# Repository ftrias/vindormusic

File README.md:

Vindor ES Source Code
=====================

This repository holds the source code, modules and PCB layouts of the Vindor ES1/2 electronic saxophone and wind instrument (clarinet, flute, trumpet, etc.). More information is available at [Vindor Music](http://vindormusic.com)

Directories
-----------

| Directory           | Contents
| ------------------- | ------------------------
| /apps               | Mobile and web apps
| /apps/juce-gui      | Main control app for Mac/Win/iOS/Android
| /apps/splayer       | Free generic MIDI player
| /firmware           | Source for firmware and related modules
| /firmware/source    | ES1/2 main source
| /firmware/external  | Non-Vindor open source libraries used
| /pcb                | KiCad source for PCB
| /shell              | Solidworks models for the shell
| /documents          | Documentation and promotional material
| /sounds             | Sound files for use on SD cards

License
-------

Unless otherwise noted, the software is Copyright (c) 2023 by Fernando Trias and Vindor Music, Inc. The software is licensed for use under the Creative Commons license available in `LICENSE.txt` and summarized on the [CC page](https://creativecommons.org/licenses/by-nc/3.0/).

This software uses external modules that are distributed according to their own licenses, which are all open source.

To summarize:
1. You may freely use this software for non-commercial purposes.
2. You must give appropriate credit to respective authors.

History
---------
This project began in 2016 to produce an affordable electronic wind instrument. At that time, the market was dominated by Yamaha and Akai. Both produced superb instruments that were prohibitively expensive for casual musicians. In addition, there were a number of small niche manufacturers targeting advanced players. Although Akai produced a low-cost USB instrument, it was large, heavy and had limited market penetration. In addition, we wanted to create an easy-to-use low-cost alternative for beginning players that would be both stand-alone and interface easily with Garageband and similar apps popular with younger musicians.

The Vindor began with a Kickstarter campaign and started being sold commercially in 2018 both online and in stores. It was covered by numerous blogs and journals, including Fast Company and the Boston Globe. In 2019, Roland release the Aerophone Mini AE-01, which although larger and slightly more expensive than the Vindor, targeted the same entry-level market. This, combined with the COVID shutdown and subsequent rise in component costs, made producing more Vindors impractical and all existing inventory was sold out by late 2020. 

By 2023, the chip market had not recovered and it still not possible to make more Vindors (the main CPU is still unavailable). Since Vindor Music closed its doors, we have decided to open source the firmware and apps, as well as the PCB, BOM and other components.

Open Source Announcement
------------------------

Vindor Music has open sourced the ES1 electronic wind instrument software and hardware. The Vindor ES1 was a low-cost entry-level electronic wind instrument that launched in 2018 and sold until 2020, a casualty of the COVID pandemic. The release includes all the source for the firmware, Android, iOS, Mac and Windows apps, as well as the BOM, schematics and PCB layout of the circuit boards. It includes everything you need to make your own ES1 and program it to do whatever you like. We hope this will inspire hobbyists to port the ES1 to a new CPU and continue the mission of providing an affordable and functional electronic wind instrument. The source can be found at https://github.com/ftrias/vindormusic.

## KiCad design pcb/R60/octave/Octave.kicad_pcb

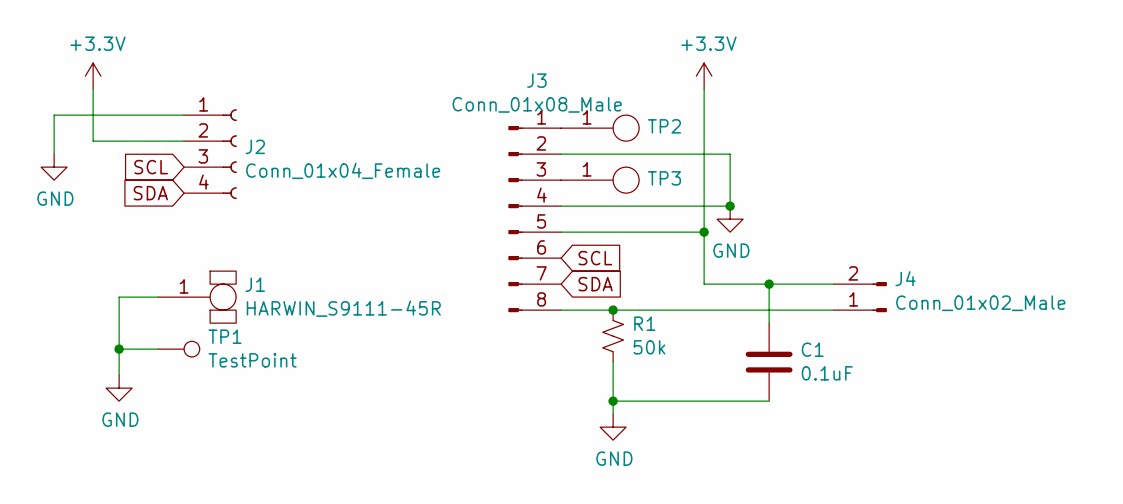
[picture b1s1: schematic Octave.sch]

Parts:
C1: 0.1uF; MF_Passives-C0603; MPN MF-CAP-0603-0.1uF
J1: HARWIN_S9111-45R; HARWIN_S9111_45R; MPN S9111-45
J2: Conn_01x04_Female; Moldex-0448120004; MPN 44812-0004
J3: Conn_01x08_Male; PinHeader_1x08_P2.54mm_Vertical; MPN MF-CON-2.54mm-01x08
J4: Conn_01x02_Male; JST_PH_S2B-PH-K_1x02_P2.00mm_Horizontal; MPN S2B-PH-K-S(LF)(SN)
R1: 50k; MF_Passives-R0603; MPN MF-RES-0603-50K
TP1: TestPoint; PinHeader_1x01_P2.54mm_Horizontal
TP2, TP3: TOUCHPAD; Vindor_Touchpad

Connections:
+3V3: C1.1, J2.2, J3.5, J4.2
GND: C1.2, J1.1, J2.1, J3.2, J3.4, R1.1, TP1.1
unnamed: J3.1, TP2.1
unnamed: J3.3, TP3.1
unnamed: J3.8, J4.1, R1.2
SCL: J2.3, J3.6
SDA: J2.4, J3.7

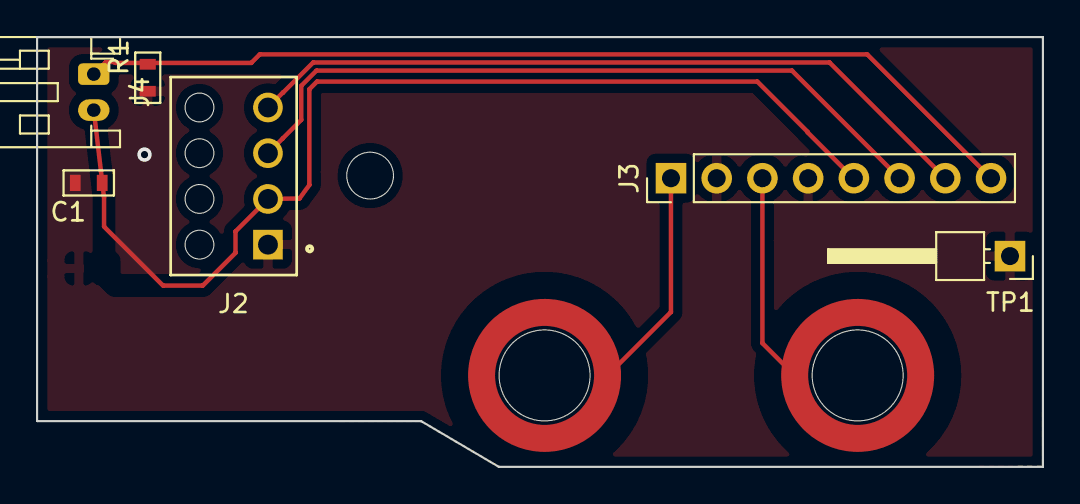
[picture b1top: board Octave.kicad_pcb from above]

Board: 2 copper layers, 55.9 x 23.9 mm, 9 parts (1 on the bottom side), 7 nets.

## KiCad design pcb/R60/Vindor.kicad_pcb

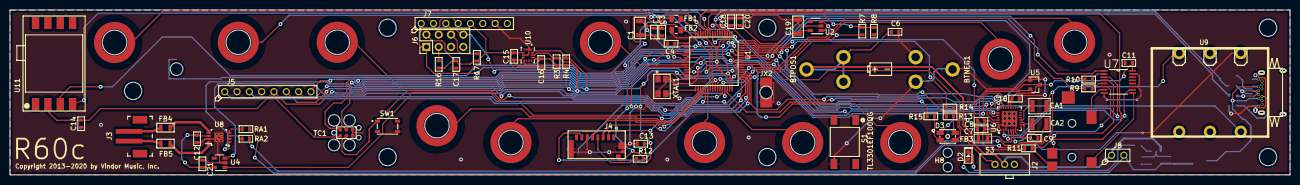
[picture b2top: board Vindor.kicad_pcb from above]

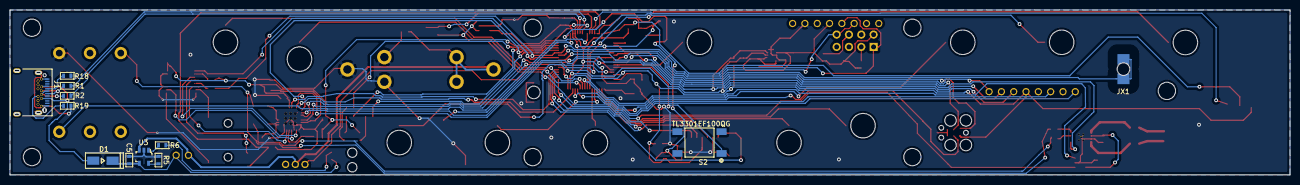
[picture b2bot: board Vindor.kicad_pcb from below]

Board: 2 copper layers, 264.0 x 34.0 mm, 100 parts (12 on the bottom side), 91 nets.

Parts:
BTNEG1: KEYSTONE 54; KEYSTONE_54
BTPOS1: KEYSTONE 54; KEYSTONE_54
C1, C19: 10 uf; MF_Passives-C1206
C2, C20, C21: 1 uf; MF_Passives-C0603
C3, C4, C7, C8, C9, C10, C11, C12, C13, C14, C15, C16, C17, C18: 0.1 uf; MF_Passives-C0603
C5, C6: 4.7 uf; MF_Passives-C0603
CA1, CA2: 100 nf; MF_Passives-C1210
D1: MF-DIO-SMA-B140; MF_Discrete_Semiconductor-SMA
D2: MF-LED-0603-RED; MF_LEDs-LED0603
D3: LED_RGB_CA_PLCC4; MF_LEDs-PLCC4
FB1, FB2: BLM21AG601SN1D; L_0805_2012Metric
FB3, FB4, FB5: BLM21AG601SN1D; MF_Passives-C0805
H1, H2, H3, H4, H5, H6, H7: MountingHole; Screw_hole
H8: MountingHole; Vindor_light_pipe
J1: 10137062-00021LF; USBC_10137062-00021LF
J2: 35RASMT4BHNTRX; SWITCHCRAFT_35RASMT4BHNTRX
J3: B2B-PH-SM4-TB(LF)(SN); PinHeader_1x2_P2mm
J4: 47309-3351; MOLEX_MICROSD_473093351
J5: 2.54mm 01x08 Female; MF_Connectors-PTH_2.54MM_01X08
J6: Conn_02x04_Odd_Even; PinHeader_2x04_P2.54mm_Vertical
J7: Conn_01x08_Female; MF_Connectors-PTH_2.54MM_01X08
J8: Conn_01x02_Male; MF_Connectors-PTH_2.54MM_01X02
JX1: S9111-45R; HARWIN_S9111_45R
JX2: S9111-45R; HARWIN_S9111_45R-TIGHT
R1, R2: 27 ohm; MF_Passives-R0603
R3, R6, R12: 470 ohm; MF_Passives-R0603
R4: 470 ohm; MF_Passives-L0603
R5: 10k ohm; MF_Passives-R0603
R7, R8: 18k ohm; MF_Passives-R0603
R9, R10: 47 ohm; MF_Passives-R0603
R11: 220 ohm; MF_Passives-R0603
R13, R14, R15: 100 ohm; MF_Passives-R0603
R16, R17: 10k ohm; MF_Passives-L0603
R18, R19: 5.1k ohm; MF_Passives-R0603
RA1, RA2: 20k ohm; MF_Passives-R0603
S1, S2: TL3301EF100QG; SOIC450P1000X730-4N
S3: 1825282-1; TE1825282-1
SW1: MF-SW-TACT-4.2MM; SW_PTS810_SJM_250_SMTR_LFS
TC1: CON_02X03_TC2030-IDC-NL; TC2030
TP1, TP2, TP3, TP4, TP5, TP6, TP7, TP8, TP9, TP10, TP11: TOUCHPAD; Vindor_Touchpad
U1: MK20DX256VLH7
U2, U4: TLV70233_SOT23-5; SOT-23-5
U3: MCP73831T-2ACI/OT; SOT-753
U5: MCP1703A; SOT-23
U6: SGTL5000XNAA3; SGTL5000
U7: TS3A5018PW; SOP65P640X120-16N
U8: TPA2005D1DGNRQ1; Vindor-MSOP-8-1EP_W3mm
U9: NMJ4HHD2 or NMJ6HHD2; NMJ6HFD2-center
U10: LSM6DS3TR; LGA-14_3x2.5mm_P0.5mm
U11: MP3V5004GP
XTAL1: ECS-160-9-42-CKM-TR

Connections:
2:AMP_SHUTDOWN: U1.57, U8.1
3:I2S_DIN: U1.28, U6.26
4:I2S_LRCLK: U1.29, U6.23
5:LED_GREEN: R14.2, U1.64
6:LED_RED: R15.2, U1.61
7:UART_RX: J6.8, J7.3, U1.59
8:UART_TX: J6.1, J7.4, R9.2, U1.60
9:I2S_DOUT: U1.62, U6.25
9:I2S_SCLK: U1.46, U6.24
10:SC_CD: J4.2, U1.49
11:SD_CMD: J4.3, U1.51
12:SD_DAT0: J4.7, U1.52
13:SD_CLK: J4.5, U1.50
14:EN_MIDI: U1.58, U7.1
21:LED_BLUE: R13.2, U1.63
22:TOUCH_HIGH: J5.1, U1.44
23:TOUCH_LOW: J5.3, U1.45
24: S2.1, U1.27
26: S1.1, U1.2
27:LDO_EN: U1.54, U4.3
28:SYS_MCLK: U1.53, U6.21
29:CTRL_CLK: J5.6, R3.2, U1.55, U6.29, U10.13
30:CTRL_DATA: J5.7, R4.2, U1.56, U6.27, U10.14
31:SD_DET: J4.12, R12.2, U1.1
+3.3VA: FB1.1, U1.13, U1.14
+4V: R7.1, S3.1, U2.1, U2.3, U4.1
A12: U1.11, U11.4
A14: J5.8, U1.18
AMP_JACK: U1.9, U9.SLEEVENORMAL
AMP_LEFT: CA1.1, RA1.2, U9.TIP
BV: R7.2, R8.1, U1.10
GNDA: FB2.1, U1.16, U11.3
HP_G: U6.4, U7.10
HP_JACK: J2.4, R11.2, U1.12
HP_L: U6.6, U7.6
HP_R: U6.2, U7.3
LGND: BTNEG1.1, C1.1, C2.1, C3.1, C4.2, C5.2, C6.2, C7.2, C8.2, C9.2, C10.2, C11.2, C12.1, C13.1, C14.1, C15.1, C16.1, C17.1, C18.1, C19.1, C20.1, C21.1, FB2.2, J1.A1, J1.A12, J1.B1, J1.B12, J1.S1, J4.6, J4.9, J4.10, J4.11, J5.2, J5.4, J7.2, J7.7, JX2.1, R5.2, R8.2, R11.1, R18.2, R19.2, S1.4, S2.4, SW1.4, TC1.5, TC1.6, U1.4, U1.15, U1.31, U1.47, U2.2, U3.2, U4.2, U5.1, U6.1, U6.3, U6.7, U6.31, U6.32, U6.EXP, U7.8, U7.11, U7.15, U8.7, U8.9, U9.SLEEVE, U10.1, U10.2, U10.3, U10.6, U10.7, XTAL1.2, XTAL1.4
LO_LEFT: CA1.2, U6.12
LO_RIGHT: CA2.2, U6.11
unnamed: BTPOS1.1, C6.1, J8.1, S3.2, U3.3
unnamed: C4.1, U1.17
unnamed: C5.1, D1.CATH, D2.ANOD, J8.2, U3.4
unnamed: C9.1, U6.10
unnamed: CA2.1, RA2.2
unnamed: D2.CATH, R6.1
unnamed: D3.2, R15.1
unnamed: D3.3, R14.1
unnamed: D3.4, R13.1
unnamed: FB3.1, U6.5
unnamed: FB4.1, J3.1
unnamed: FB4.2, U8.5
unnamed: FB5.1, J3.2
unnamed: FB5.2, U8.8
unnamed: J1.A5, R18.1
unnamed: J1.B5, R19.1
unnamed: J2.1, U7.9
unnamed: J2.2, U7.4
unnamed: J2.3, U7.7
unnamed: J6.3, R16.1
unnamed: J6.6, R17.2
unnamed: JX1.1, U1.24
unnamed: R1.1, U1.6
unnamed: R2.1, U1.5
unnamed: R5.1, U3.5
unnamed: R6.2, U3.1
unnamed: R9.1, U7.5
unnamed: R10.1, U7.2
unnamed: RA1.1, U8.4
unnamed: RA2.1, U8.3
unnamed: TP1.1, U1.39
unnamed: TP2.1, U1.40
unnamed: TP3.1, U1.41
unnamed: TP4.1, U1.35
unnamed: TP5.1, U1.36
unnamed: TP6.1, U1.26
unnamed: TP7.1, U1.38
unnamed: TP8.1, U1.37
unnamed: TP9.1, U1.23
unnamed: TP10.1, U1.43
unnamed: TP11.1, U1.42
unnamed: U1.32, XTAL1.1
unnamed: U1.33, XTAL1.3
RESET_B: SW1.1, TC1.3, U1.34
SWDCLK: TC1.4, U1.22
SWDIO: TC1.2, U1.25
USB_DM: J1.A7, J1.B7, R1.2
USB_DP: J1.A6, J1.B6, R2.2
USB_VBUS: D1.ANOD, J1.A4, J1.A9, J1.B4, J1.B9
VCC33: C1.2, C2.2, C3.2, C7.1, C10.1, C11.1, C13.2, C14.2, C15.2, C16.2, C17.2, C18.2, C19.2, C20.2, D3.1, FB1.2, FB3.2, J4.4, J5.5, J6.2, J7.5, R3.1, R4.1, R10.2, R12.1, R16.2, R17.1, TC1.1, U1.3, U1.7, U1.21, U1.30, U1.48, U2.5, U5.3, U6.20, U7.16, U10.5, U10.8, U10.12, U11.2
VCC_1.8: C8.1, U5.2, U6.30
VCC_3.3AUD: C12.2, C21.2, U4.5, U8.6

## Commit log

2023-01-16 Remove extra file
2024-02-22 Add shell and documents

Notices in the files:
pcb/R60/Vindor.kicad_pcb:
Copyright 2013-2020 by Vindor Music, Inc.
